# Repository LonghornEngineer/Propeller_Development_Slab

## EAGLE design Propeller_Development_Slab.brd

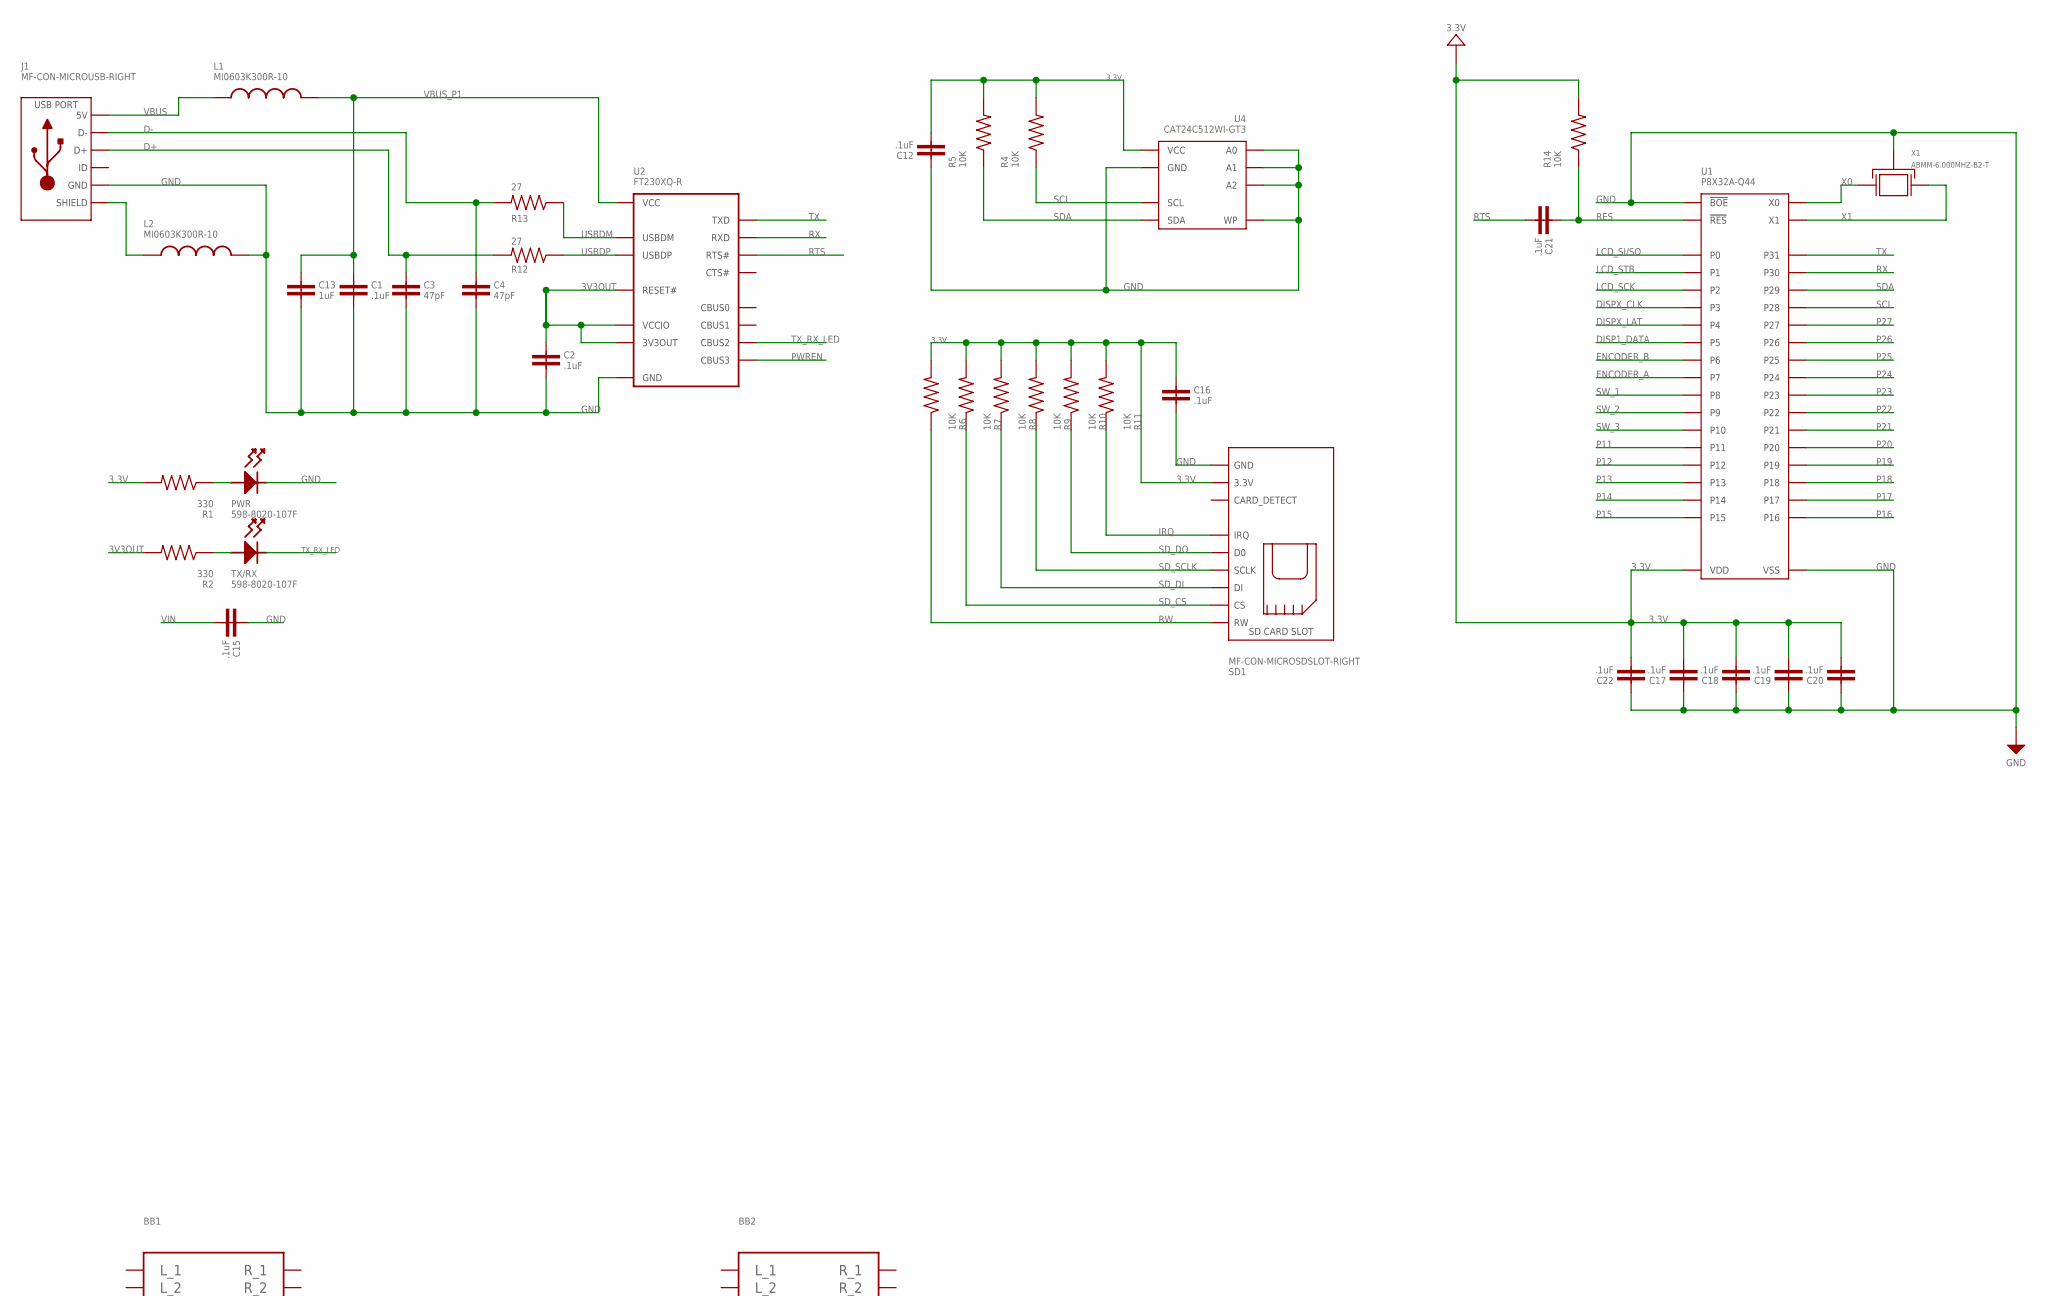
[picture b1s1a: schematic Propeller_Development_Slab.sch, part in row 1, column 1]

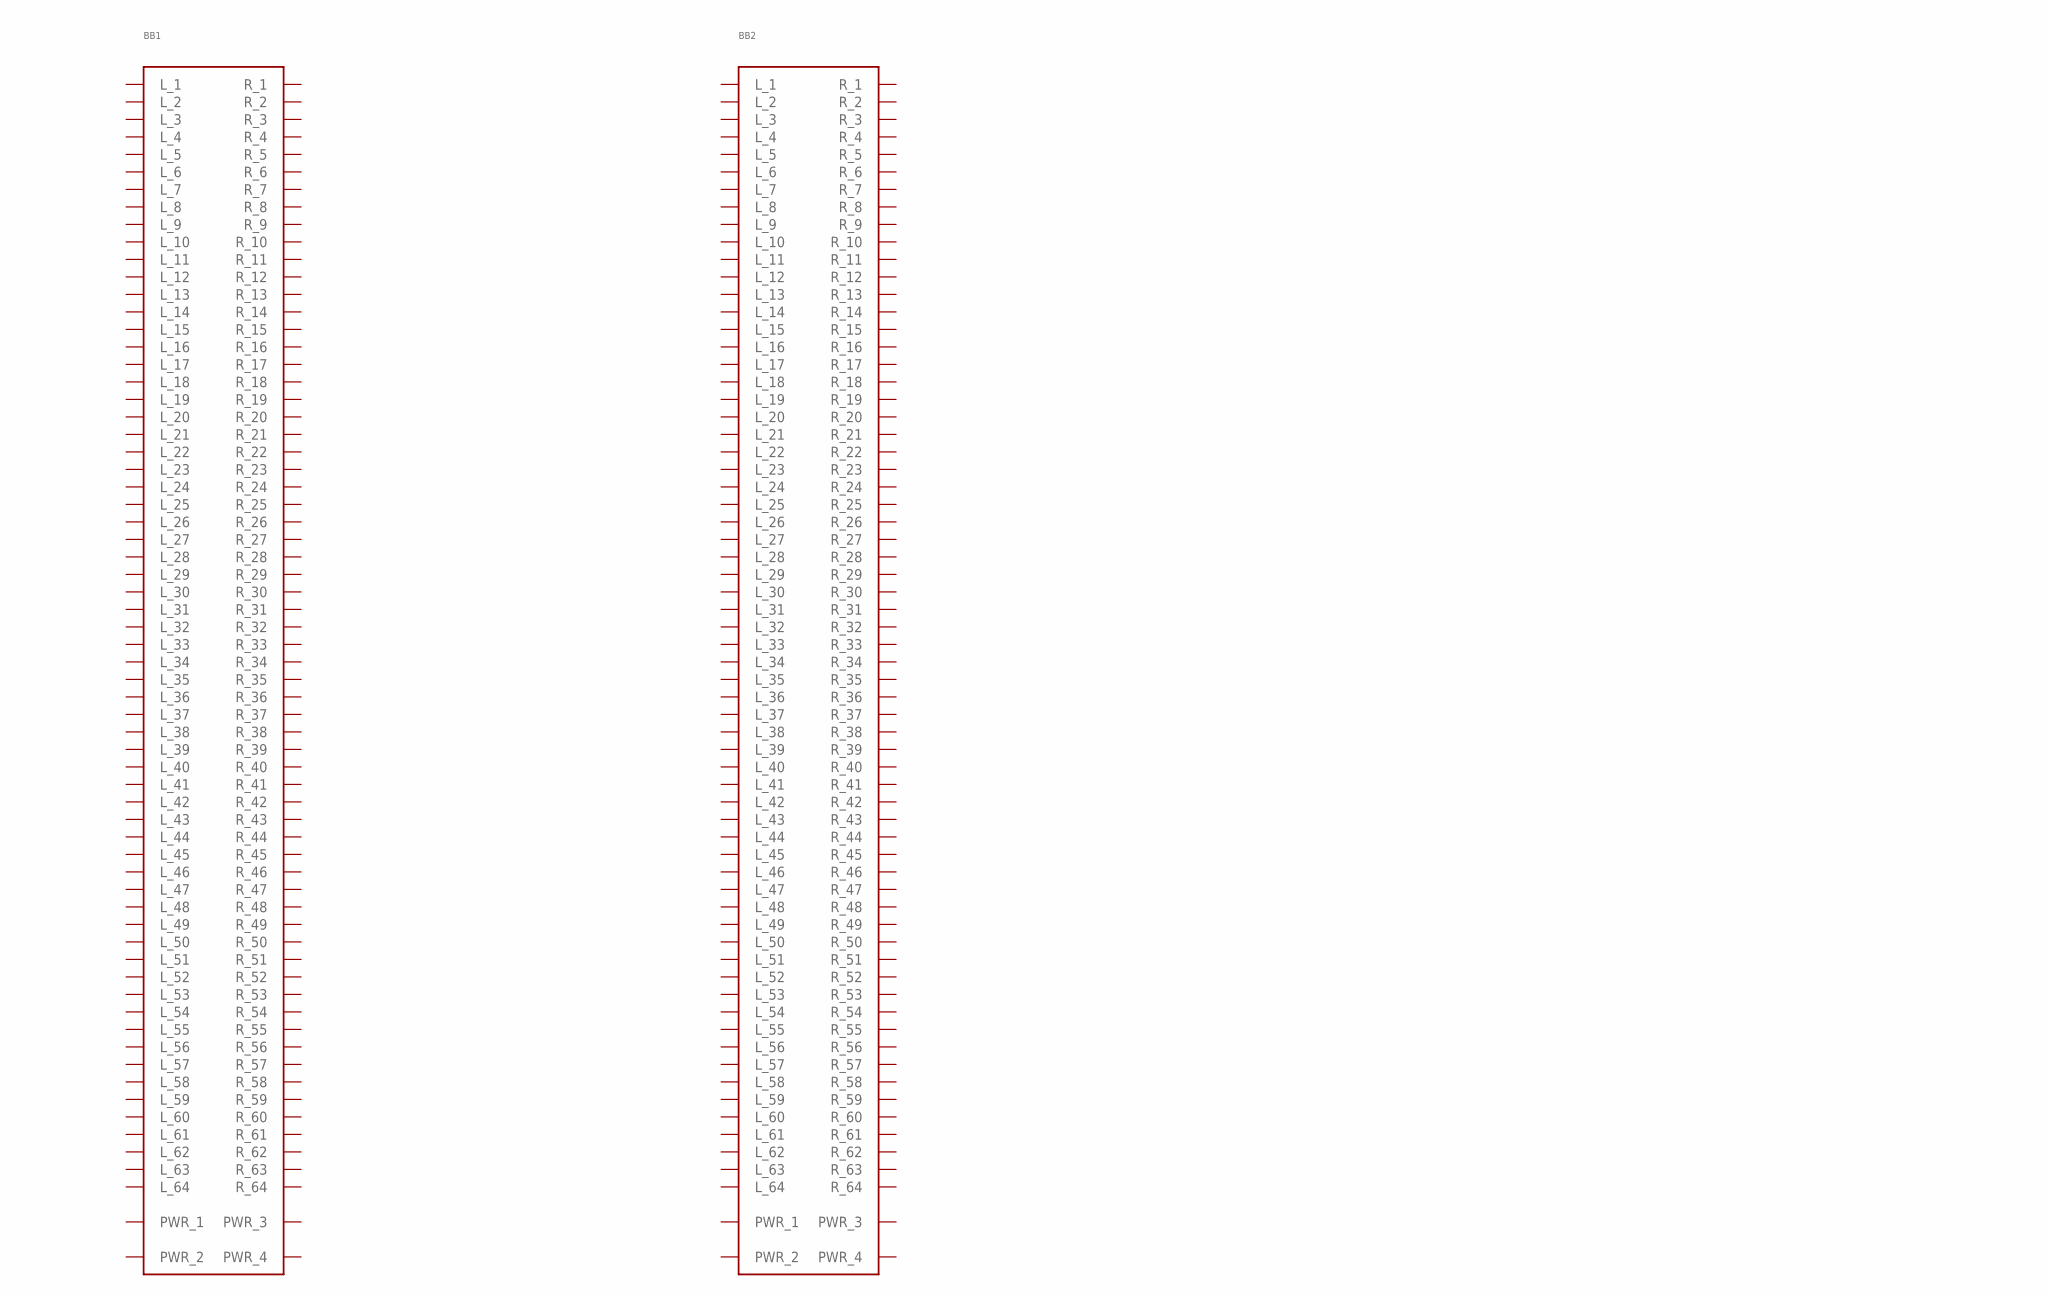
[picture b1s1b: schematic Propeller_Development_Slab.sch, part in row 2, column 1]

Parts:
BB1, BB2: BREADBOARD_0165-4214-7-9010; 0165-4214-7-9010
C1, C2, C12, C15, C16, C17, C18, C19, C20, C21, C22: .1uF; 0805
C3, C4: 47pF; 0805
C13: 1uF; 0805
J1: MF-CON-MICROUSB-RIGHT; MICROUSB-RIGHT
L1, L2: MI0603K300R-10; 0603
PWR: 598-8020-107F; LED_0805
R1, R2: 330; 0805
R4, R5, R6, R7, R8, R9, R10, R11, R14: 10K; 0805
R12, R13: 27; 0805
SD1: MF-CON-MICROSDSLOT-RIGHT; MICROSDSLOT-RIGHT
TX/RX: 598-8020-107F; LED_0805
U1: P8X32A-Q44; P8X32A_LQFP-44
U2: FT230XQ-R; FT230X_QFN-16
U4: CAT24C512WI-GT3; SOIC-8_W
X1: ABMM-6.000MHZ-B2-T; 7MMX5MM

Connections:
3.3V: C12.2, C16.1, C17.2, C18.2, C19.2, C20.2, C22.2, R1.2, R4.2, R5.2, R6.2, R7.2, R8.2, R9.2, R10.2, R11.2, R14.2, SD1.PIN4 (3.3V), U1.8 (VDD), U1.18 (VDD), U1.30 (VDD), U1.40 (VDD), U4.8 (VCC)
3V3OUT: C2.1, R2.2, U2.1 (VCCIO), U2.8 (3V3OUT), U2.9 (RESET#)
D+: C3.1, J1.3 (D+), R12.2
D-: C4.1, J1.2 (D-), R13.2
DISP1_DATA: U1.2 (P5)
DISPX_CLK: U1.44 (P3)
DISPX_LAT: U1.1 (P4)
ENCODER_A: U1.4 (P7)
ENCODER_B: U1.3 (P6)
GND: C1.2, C2.2, C3.2, C4.2, C12.1, C13.2, C15.1, C16.2, C17.1, C18.1, C19.1, C20.1, C22.1, J1.5 (GND), L2.2, PWR.CATHODE, SD1.G0 (GND), SD1.G1 (GND), SD1.PIN6 (GND), U1.5 (VSS), U1.6 (!BOE), U1.17 (VSS), U1.27 (VSS), U1.39 (VSS), U2.3 (GND), U2.13 (GND), U2.PAD (GND), U4.1 (A0), U4.2 (A1), U4.3 (A2), U4.4 (GND), U4.7 (WP), X1.P$2 (GND), X1.P$4 (GND)
IRQ: R11.1, SD1.PIN8 (IRQ)
LCD_SCK: U1.43 (P2)
LCD_SI/SO: U1.41 (P0)
LCD_STB: U1.42 (P1)
unnamed: PWR.ANODE, R1.1
unnamed: R2.1, TX/RX.ANODE
unnamed: J1.S1 (SLD), J1.S2 (SLD), J1.S3 (SLD), J1.S4 (SLD), J1.S5 (SLD), J1.S6 (SLD), L2.1
P11: U1.12 (P11)
P12: U1.13 (P12)
P13: U1.14 (P13)
P14: U1.15 (P14)
P15: U1.16 (P15)
P16: U1.19 (P16)
P17: U1.20 (P17)
P18: U1.21 (P18)
P19: U1.22 (P19)
P20: U1.23 (P20)
P21: U1.24 (P21)
P22: U1.25 (P22)
P23: U1.26 (P23)
P24: U1.31 (P24)
P25: U1.32 (P25)
P26: U1.33 (P26)
P27: U1.34 (P27)
PWREN: U2.14 (CBUS3)
RES: C21.1, R14.1, U1.7 (!RES)
RTS: C21.2, U2.16 (RTS#)
RW: R6.1, SD1.PIN1 (RW)
RX: U1.37 (P30), U2.2 (RXD)
SCL: R4.1, U1.35 (P28), U4.6 (SCL)
SDA: R5.1, U1.36 (P29), U4.5 (SDA)
SD_CS: R7.1, SD1.PIN2 (CS)
SD_DI: R8.1, SD1.PIN3 (DI)
SD_DO: R10.1, SD1.PIN7 (D0)
SD_SCLK: R9.1, SD1.PIN5 (SCLK)
SW_1: U1.9 (P8)
SW_2: U1.10 (P9)
SW_3: U1.11 (P10)
TX: U1.38 (P31), U2.15 (TXD)
TX_RX_LED: TX/RX.CATHODE, U2.5 (CBUS2)
USBDM: R13.1, U2.7 (USBDM)
USBDP: R12.1, U2.6 (USBDP)
VBUS: J1.1 (5V), L1.1
VBUS_P1: C1.1, C13.1, L1.2, U2.10 (VCC)
VIN: C15.2
X0: U1.29 (X0), X1.P$3 (X1)
X1: U1.28 (X1), X1.P$1 (X0)

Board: 2 copper layers, 39 parts (0 on the bottom side), 27 nets, no tracks yet.

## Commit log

2016-06-23 first push. need more parts!
